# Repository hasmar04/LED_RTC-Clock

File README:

# LED Matrix + RTC Clock
## DS3231 RTC Module and 32x16 Pixel LED Matrix

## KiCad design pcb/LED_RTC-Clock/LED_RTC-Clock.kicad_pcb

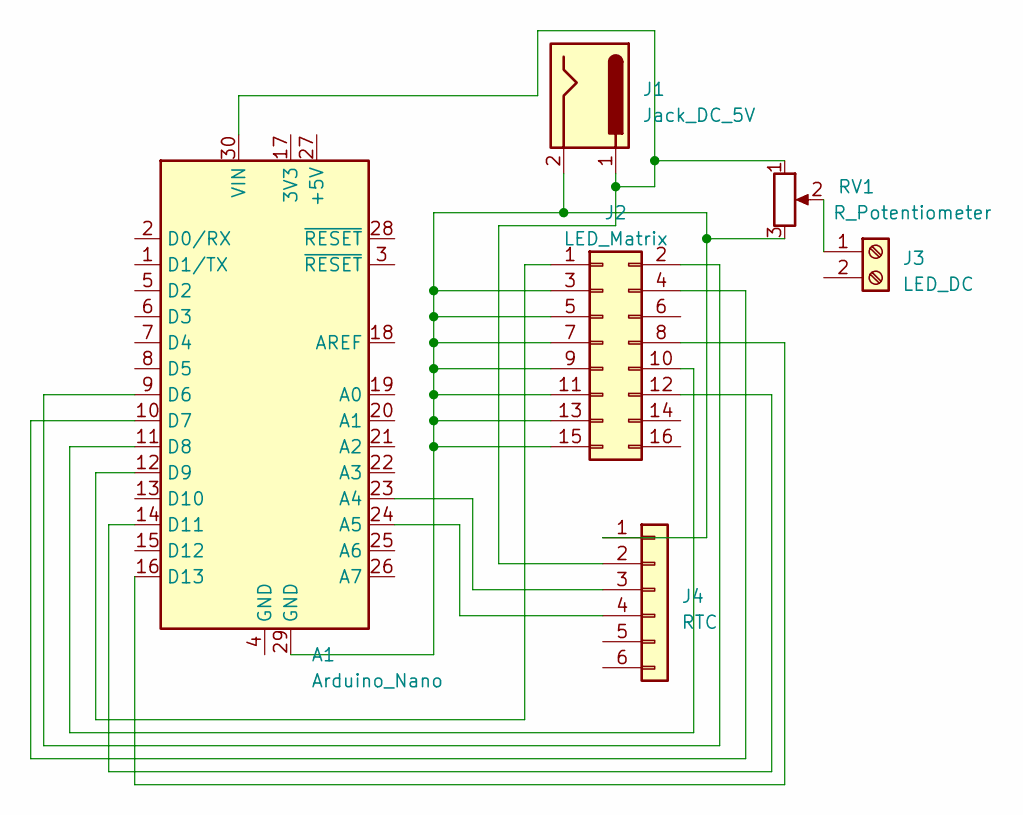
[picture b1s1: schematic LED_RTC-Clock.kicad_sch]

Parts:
A1: Arduino_Nano
J1: Jack_DC_5V; BarrelJack_Horizontal
J2: LED_Matrix; IDC-Header_2x08_P2.54mm_Vertical
J3: LED_DC; TerminalBlock_bornier-2_P5.08mm
J4: RTC; PinHeader_1x06_P2.00mm_Vertical
RV1: R_Potentiometer; Potentiometer_Alps_RK09L_Single_Horizontal

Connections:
unnamed: A1.23 (A4), J4.3 (SDA)
unnamed: A1.24 (A5), J4.4 (SCL)
unnamed: A1.9 (D6), J2.2 (GND)
unnamed: A1.10 (D7), J2.4 (GND)
unnamed: A1.11 (D8), J2.10 (B)
unnamed: A1.12 (D9), J2.1 (OE)
unnamed: A1.14 (D11), J2.12 (S)
unnamed: A1.16 (D13), J2.8 (GND)
unnamed: A1.30 (VIN), J1.1, J4.2 (VCC), RV1.1
unnamed: A1.29 (GND), J1.2, J2.3 (GND), J2.5 (GND), J2.7 (GND), J2.9 (A), J2.11 (C), J2.13 (L), J2.15 (G), J4.1 (GND), RV1.3
unnamed: J3.1, RV1.2

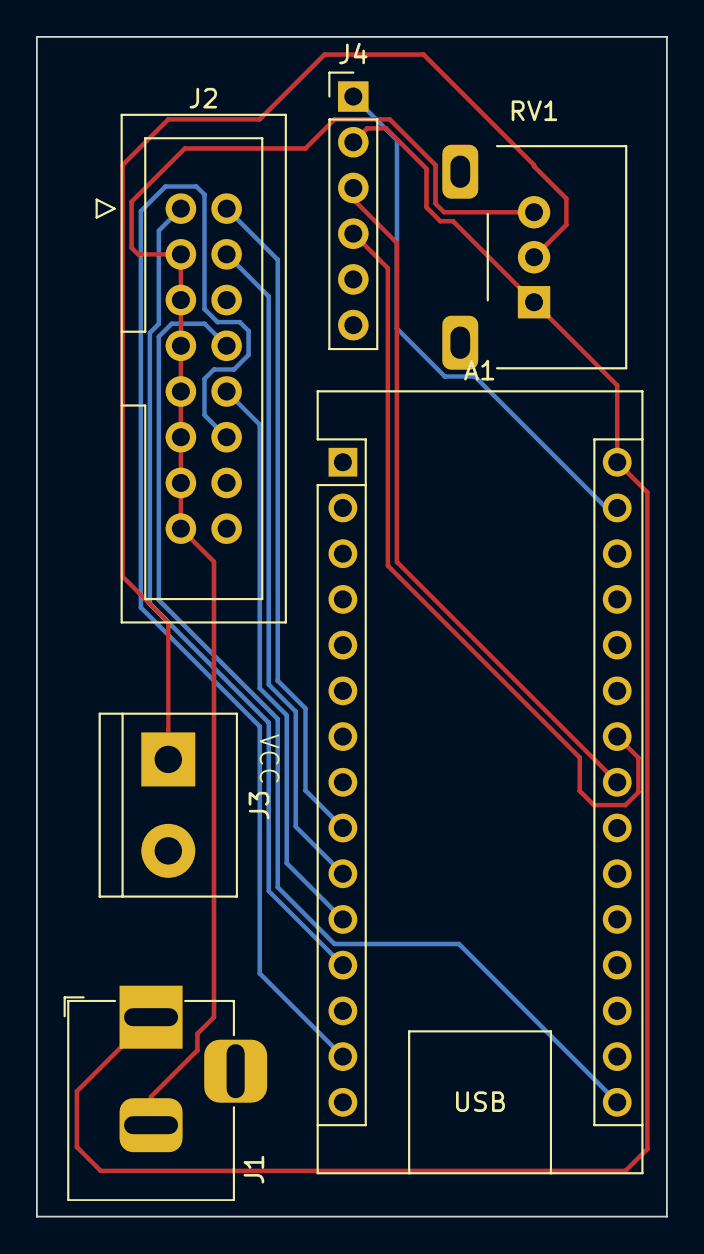
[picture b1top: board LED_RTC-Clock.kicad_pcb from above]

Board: 2 copper layers, 35.0 x 65.5 mm, 6 parts (0 on the bottom side), 11 nets.

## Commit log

2023-03-15 Updated README with extra content and proper formatting
2023-03-15 Rename README to README.md
2023-03-15 Initial Version
    Finalises code to show date and time on matrix as obtained from RTC module.
2023-03-17 Added leadingZero function
    Added leadingZero function which allows for times and dates to be displayed correctly when they are less than 10.
    Also tidied up and removed some commented code from previous debugging.
2023-03-17 Update .gitignore
    Updated gitignore to include files for KiCAD
2023-03-17 Created PCB and Schematics (WIP)
    Added PCB design and schematics to the repo for a custom board that would allow the connection of all the components together in a tidy way.
2023-03-17 Updated doc comments
2023-03-17 Removed flicker of LEDs
    Reduced timer length which removed (or at least significantly reduced) flicker in the LEDs.
2023-03-17 Updated debug log format
    Put both the time and date from each log onto the same serial line
2023-03-18 Updated PCB and Schematic
    Updated the PCB and schematics to add a potentiometer for brightness control. Also tidied up traces, modified silkscreens and finalised board layout. Silkscreened V1.0
2023-03-18 Added *.zip to gitignore
    Prevents exported pcb packages from being uploaded
2023-03-19 Reduced flicker of LEDs
    loop() still runs every second but it only updates the screen on the minute to reduce flickering from screen updates.
2023-04-04 Updated PCB to V1.1
    I received the manufactured PCBs and found that I had selected the incorrect pin spacing for the RTC header. Updated the Pin spacing from 2mm to 2.54mm and re-routed the affected traces.
2023-05-10 Expanded comments
    Expanded comments about setting time to make it more clear what each part of the string represents.
2025-01-30 Added how to set time to Serial startup output
